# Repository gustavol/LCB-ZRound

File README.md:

# LCB-ZRound
Sketch to use Lap Counter BR transponders on ZRound
Sistema de cronometragem compativel com LCB e protocolo de comunicacao compativel com LapZ

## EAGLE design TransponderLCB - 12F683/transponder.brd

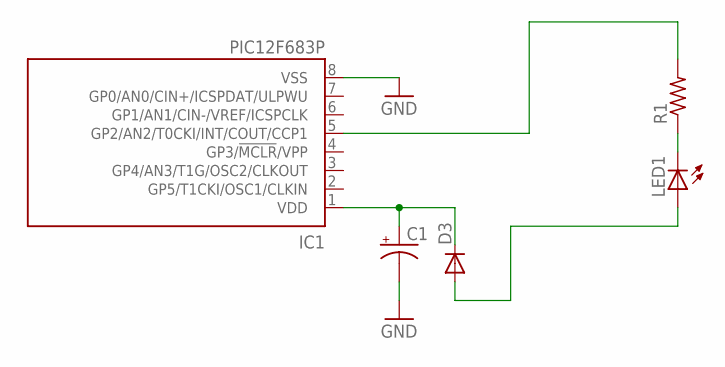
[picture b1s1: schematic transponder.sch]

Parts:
C1: CPOL-US153CLV-0505; 153CLV-0505
D3: DIODE-DO-214AC; DO-214AC
IC1: PIC12F683P; DIL8
LED1: LED3MM
R1: R-US_M0805; M0805

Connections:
GND: C1.-, IC1.8 (VSS)
unnamed: C1.+, D3.C, IC1.1 (VDD)
unnamed: LED1.K (C), R1.1
unnamed: D3.A, LED1.A
unnamed: IC1.5 (GP2/AN2/T0CKI/INT/COUT/CCP1), R1.2

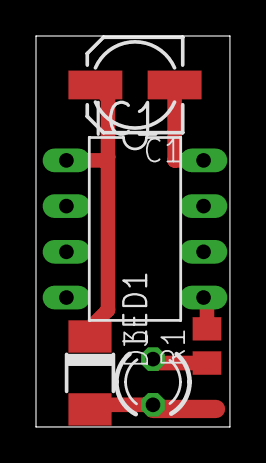
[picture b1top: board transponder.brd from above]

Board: 2 copper layers, 10.8 x 21.7 mm, 5 parts (0 on the bottom side), 5 nets.

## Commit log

2018-07-09 Rename forkSantos-LCBZround.ino to LCBZround.ino
2018-07-09 Add files via upload
    Transponder compativel com LCB utilizando PIC16F683 - Placa e esquema desenhados no Eagle Cad
